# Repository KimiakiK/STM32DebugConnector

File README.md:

# STM32 Debug Connector

# Features
- STLINKとターゲットボードを5pinで接続
- USBを接続して電源給電

# Photos

## PCB
- V2.0

- V1.0

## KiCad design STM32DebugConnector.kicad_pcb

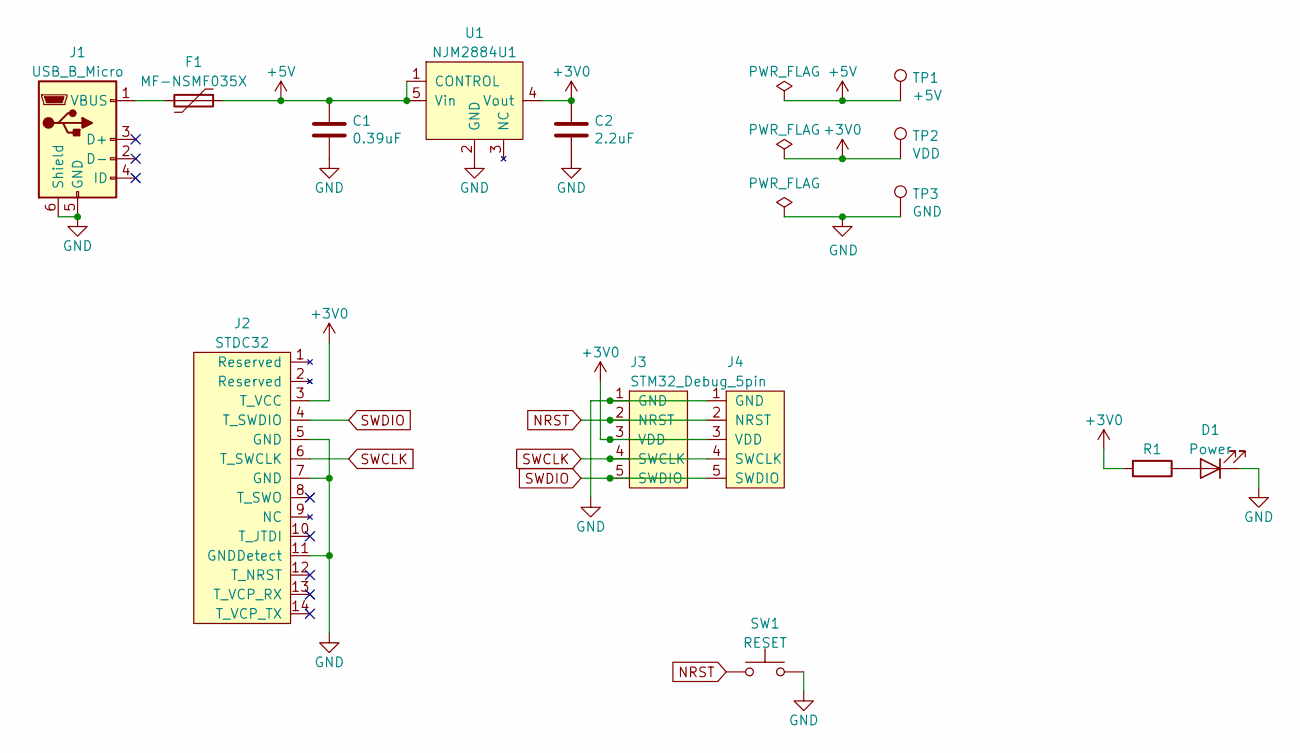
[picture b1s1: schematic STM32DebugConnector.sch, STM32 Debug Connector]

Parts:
C1: 0.39uF; C_0603_1608Metric_Pad1.05x0.95mm_HandSolder
C2: 2.2uF; C_0805_2012Metric_Pad1.15x1.40mm_HandSolder
D1: Power; LED_0603_1608Metric_Pad1.05x0.95mm_HandSolder
F1: MF-NSMF035X; Fuse_1206_3216Metric_Pad1.42x1.75mm_HandSolder
J1: USB_B_Micro; ZX62-B-5PA
J2: STDC32; PinHeader_2x07_P1.27mm_Vertical
J3, J4: STM32_Debug_5pin
R1: R; R_0603_1608Metric_Pad1.05x0.95mm_HandSolder
SW1: RESET; Switch_TS665SG-S
TP1: +5V; TestPoint_THTPad_D2.0mm_Drill1.0mm
TP2: VDD; TestPoint_THTPad_D2.0mm_Drill1.0mm
TP3: GND; TestPoint_THTPad_D2.0mm_Drill1.0mm
U1: NJM2884U1; SOT-89-5

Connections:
+3V0: C2.1, J2.3 (T_VCC), J3.3 (VDD), J4.3 (VDD), R1.2, TP2.1, U1.4 (Vout)
+5V: C1.1, F1.1, TP1.1, U1.1 (CONTROL), U1.5 (Vin)
GND: C1.2, C2.2, D1.1 (K), J1.5 (GND), J1.6 (Shield), J2.5 (GND), J2.7 (GND), J2.11 (GNDDetect), J3.1 (GND), J4.1 (GND), SW1.2, TP3.1, U1.2 (GND)
NRST: J3.2 (NRST), J4.2 (NRST), SW1.1
unnamed: D1.2 (A), R1.1
unnamed: F1.2, J1.1 (VBUS)
SWCLK: J2.6 (T_SWCLK), J3.4 (SWCLK), J4.4 (SWCLK)
SWDIO: J2.4 (T_SWDIO), J3.5 (SWDIO), J4.5 (SWDIO)

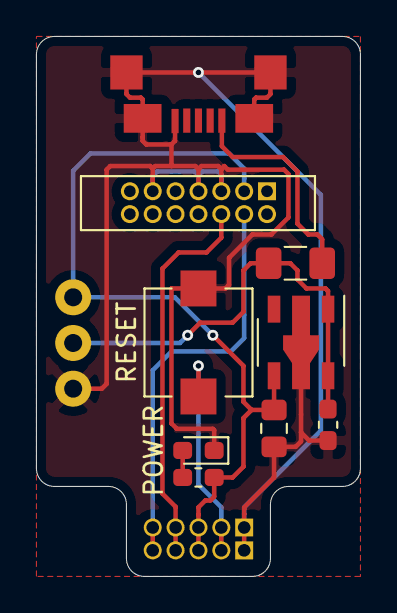
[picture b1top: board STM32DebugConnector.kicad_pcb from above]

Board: 2 copper layers, 18.0 x 30.0 mm, 14 parts (0 on the bottom side), 8 nets.

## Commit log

2021-03-21 基板 V1.0
2021-03-21 基板 V2.0
2021-04-29 Add images
